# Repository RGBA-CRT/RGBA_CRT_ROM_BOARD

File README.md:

# RGBA_CRT ROM BOARD
+ 27C322 64Mbit ROM board for 8bit databus system
**※まだ不安定です**

# about
+ 27C322を40ピンのピンヘッダに引き出す基板です
+ レトロコンシューマゲーム機やレトロコンピュータでの使用を想定しています
+ 引き出したピンヘッダにはIDC 40ピンリボンケーブルを接続します
	+ IDEケーブル（40芯, 全ピンが結線されているもの）が使用可能です
+ その他
	+ データバスは8bitに変換されます
	+ 27C322を2つ使って64Mbitに対応
	+ ROMのセレクトスイッチ搭載
+ この基板に対応したROMライターはこちら
	+ https://github.com/RGBA-CRT/FT232H-EPROM-Prog

# PIN ROM Interface pinout

+ data bus: 8bit
+ address bus: A0-A23 24bit
+ control bus: CE / OE / WE
+ VPP signal supported

# ROM select switch
+ A20, A21, A22の制御スイッチがあります
	+ A20 ... 8Mbit単位切り替え
	+ A21 ... 16Mbit単位切り替え
	+ A22 ... 32Mbit単位切り替え（EPROM切り替え）
+ FREEにするとそのアドレスビットの制御を機器側に委ねます
+ FIXにするとそのアドレスビットの制御をHIGH/LOWスイッチに委ねます
+ 使用例
	+ 1つの64MbitのROMとして基板を使いたい
		+ A20, A21, A22をすべてFREEにする
	+ 4つの16MbitのROMとして基板を使いたい
		+ A20をFREEにする
		+ A21, A22はFIXにする
			+ 2つのHIGH/LOWスイッチで4分割したROMの選択を行う

# 使用例

# other
+ SNES/SFCのExHiROMとして使用する場合は、ROM焼き時と実機実行時でROM L, ROM Hを逆に取り付ける必要があります。
	+ ROMライターはファイルの順の通り次のように書き込みます
		+ ROM L: SNES BANK $C0-$FF
		+ ROM H: SNES BANK $40-$7F
	+ したがってSFCのカートリッジとして使うときにはROM LとROM Hを逆にする必要があります
+ おまけ
	+ この40 PIN ROM Interfaceに対応したユニバーサル基板

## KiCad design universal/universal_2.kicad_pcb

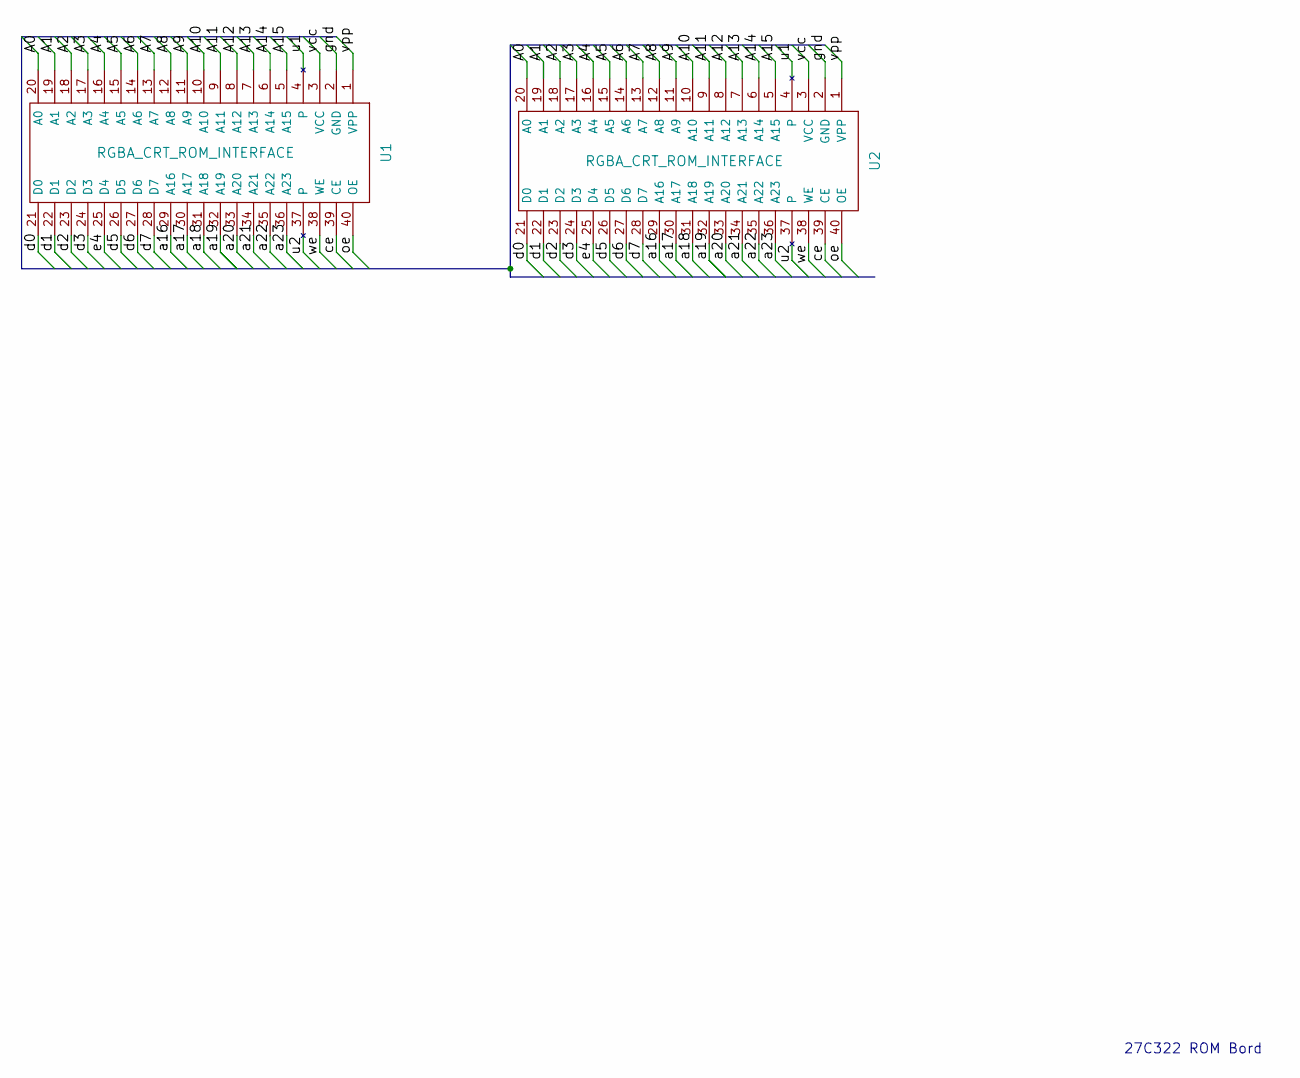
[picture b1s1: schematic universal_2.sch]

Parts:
U1: RGBA_CRT_ROM_INTERFACE
U2: RGBA_CRT_ROM_INTERFACE; RGBA_CRT_ROM_INTERFACE_DEBUG_HEDADER

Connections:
/A0: U1.20 (A0), U2.20 (A0)
/A1: U1.19 (A1), U2.19 (A1)
/A2: U1.18 (A2), U2.18 (A2)
/A3: U1.17 (A3), U2.17 (A3)
/A4: U1.16 (A4), U2.16 (A4)
/A5: U1.15 (A5), U2.15 (A5)
/A6: U1.14 (A6), U2.14 (A6)
/A7: U1.13 (A7), U2.13 (A7)
/A8: U1.12 (A8), U2.12 (A8)
/A9: U1.11 (A9), U2.11 (A9)
/A10: U1.10 (A10), U2.10 (A10)
/A11: U1.9 (A11), U2.9 (A11)
/A12: U1.8 (A12), U2.8 (A12)
/A13: U1.7 (A13), U2.7 (A13)
/A14: U1.6 (A14), U2.6 (A14)
/A15: U1.5 (A15), U2.5 (A15)
/a16: U1.29 (A16), U2.29 (A16)
/a17: U1.30 (A17), U2.30 (A17)
/a18: U1.31 (A18), U2.31 (A18)
/a19: U1.32 (A19), U2.32 (A19)
/a20: U1.33 (A20), U2.33 (A20)
/a21: U1.34 (A21), U2.34 (A21)
/a22: U1.35 (A22), U2.35 (A22)
/a23: U1.36 (A23), U2.36 (A23)
/ce: U1.39 (CE), U2.39 (CE)
/d0: U1.21 (D0), U2.21 (D0)
/d1: U1.22 (D1), U2.22 (D1)
/d2: U1.23 (D2), U2.23 (D2)
/d3: U1.24 (D3), U2.24 (D3)
/d5: U1.26 (D5), U2.26 (D5)
/d6: U1.27 (D6), U2.27 (D6)
/d7: U1.28 (D7), U2.28 (D7)
/e4: U1.25 (D4), U2.25 (D4)
/gnd: U1.2 (GND), U2.2 (GND)
/oe: U1.40 (OE), U2.40 (OE)
/u1: U1.4, U2.4
/u2: U1.37, U2.37
/vcc: U1.3 (VCC), U2.3 (VCC)
/vpp: U1.1 (VPP), U2.1 (VPP)
/we: U1.38 (WE), U2.38 (WE)

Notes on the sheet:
27C322 ROM Bord

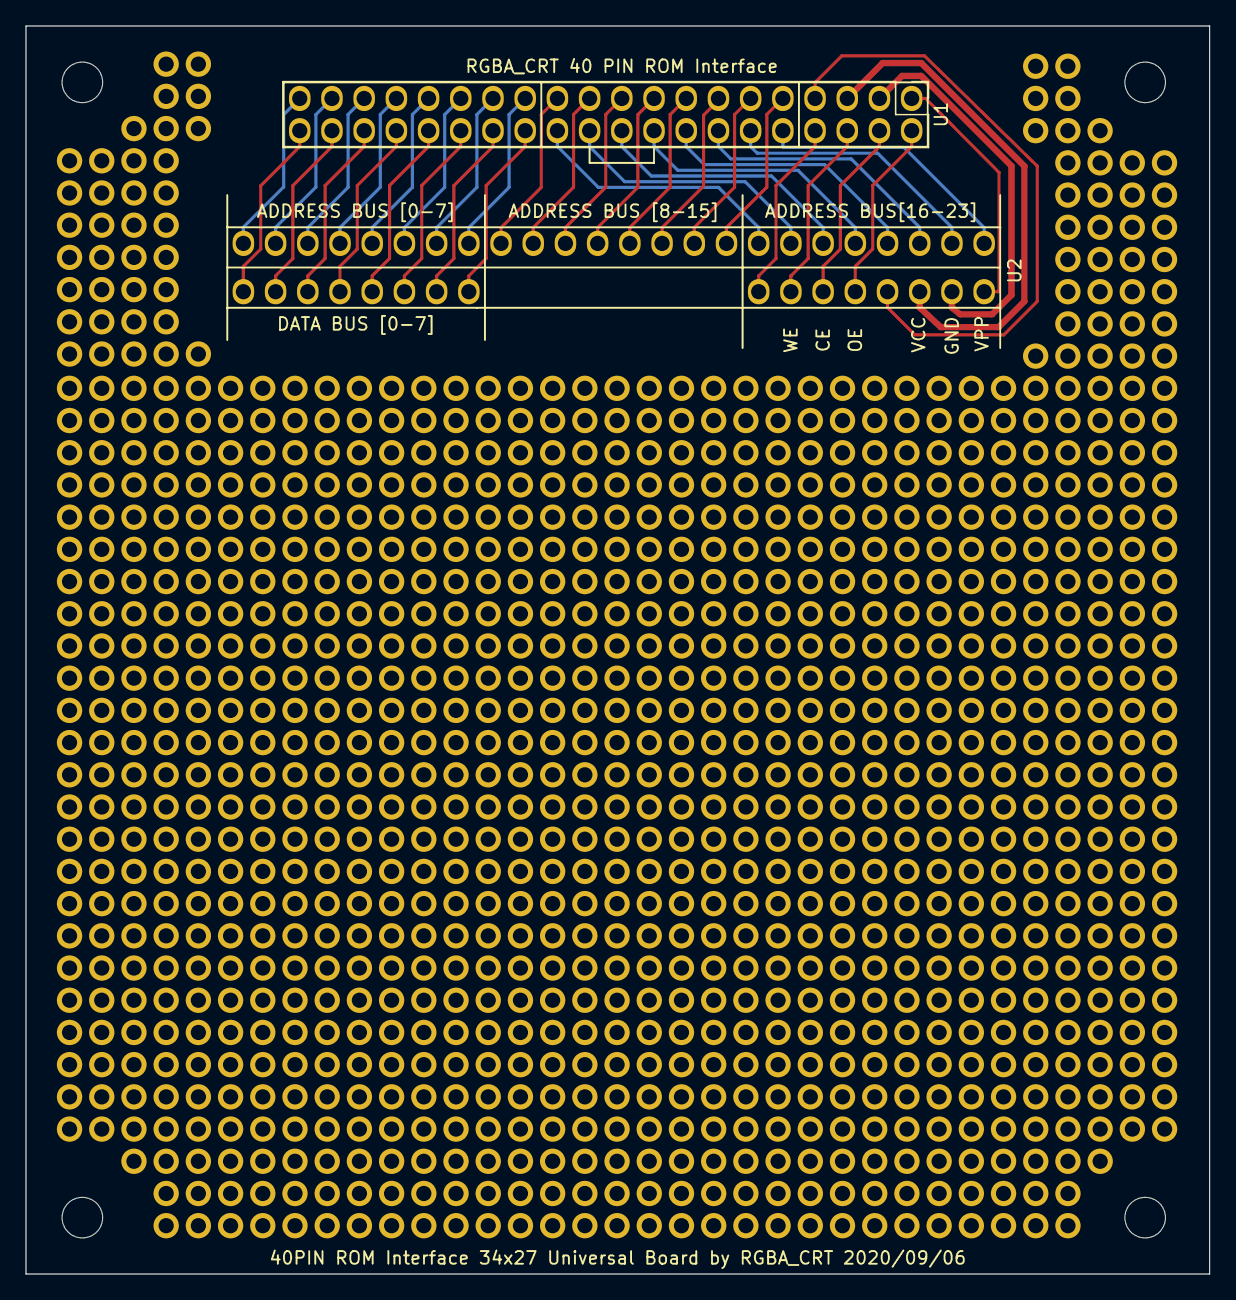
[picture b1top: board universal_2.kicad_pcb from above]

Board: 2 copper layers, 93.3 x 98.4 mm, 9 parts (0 on the bottom side), 40 nets.

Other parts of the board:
HOLE1, HOLE2, HOLE3, HOLE4: MountingHole_3.2mm_M3
LEFT: SolderWirePad_4xSquare_0-8mmDrill
RIGHT: SolderWirePad_4xSquare_0-8mmDrill
UBIVERSAL: SolderWirePad_4xSquare_0-8mmDrill

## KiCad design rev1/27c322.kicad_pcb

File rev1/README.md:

# RGBA_CRT_ROM_BOARD rev1
+ one ROM
+ 2 ROM select switch
+ low bytes are mapped to 0x000000-0x1FFFFF
+ high bytes are mapped to 0x200000-0x3FFFFF

# garber
[27c322Bord.zip](27c322Bord.zip)

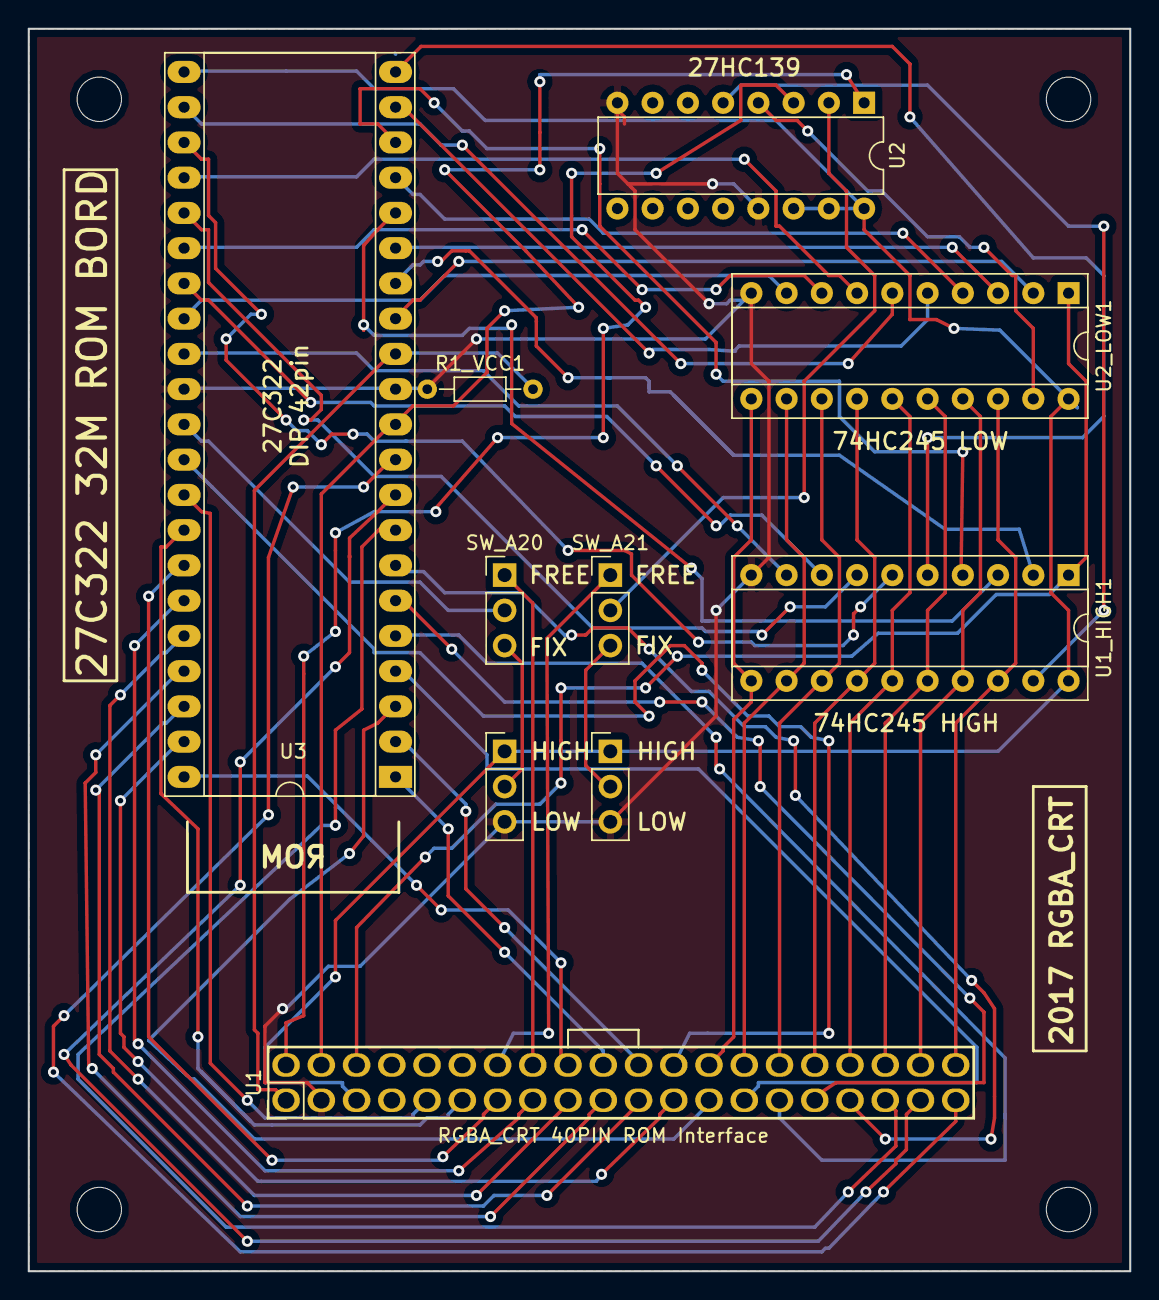
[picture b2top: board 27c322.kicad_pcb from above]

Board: 2 copper layers, 79.4 x 89.5 mm, 14 parts (0 on the bottom side), 58 nets.

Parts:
MOUNTU+: MountingHole_3.2mm_M3
MOUNT_BR: MountingHole_3.2mm_M3
MOUNT_LB: MountingHole_3.2mm_M3
MOUNT_UR: MountingHole_3.2mm_M3
R1_VCC1: R; R_Axial_DIN0204_L3.6mm_D1.6mm_P7.62mm_Horizontal
SWA21_HL1: Switch_SPDT_x2; Pin_Header_Straight_1x03_Pitch2.54mm
SW_A20, SW_A20_HL1, SW_A21: Switch_SPDT_x2; Pin_Header_Straight_1x03_Pitch2.54mm
U1: RGBA_CRT_ROM_INTERFACE
U1_HIGH1, U2_LOW1: 74HC245; DIP-20_W7.62mm_Socket
U2: 74LS139; DIP-16_W7.62mm
U3: 27C322; DIP-42_W15.24mm_Socket_LongPads

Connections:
+5V: SWA21_HL1.1, SW_A20_HL1.1, U1.3, U1_HIGH1.20, U2.14, U2.15, U2.16, U2_LOW1.20, U3.22
/A0: U1.20, U3.10
/A1: U1.19, U3.9
/A2: U1.18, U3.8
/A3: U1.17, U3.7
/A4: U1.16, U3.6
/A5: U1.15, U3.5
/A6: U1.14, U3.4
/A7: U1.13, U3.3
/A8: U1.12, U3.41
/A9: U1.11, U3.40
/A10: U1.10, U3.39
/A11: U1.9, U3.38
/A12: U1.8, U3.37
/A13: U1.7, U3.36
/A14: U1.6, U3.35
/A15: U1.5, U3.34
/A16: U1.29, U3.33
/A17: U1.30, U3.2
/A18: U1.31, U3.1
/A19: U1.32, U3.42
/A20: SW_A20.2, U3.32
/A21: SW_A21.2, U2.2
/D0: U1.21, U1_HIGH1.18, U2_LOW1.18
/D1: U1.22, U1_HIGH1.17, U2_LOW1.17
/D2: U1.23, U1_HIGH1.16, U2_LOW1.16
/D3: U1.24, U1_HIGH1.15, U2_LOW1.15
/D4: U1.25, U1_HIGH1.14, U2_LOW1.14
/D5: U1.26, U1_HIGH1.13, U2_LOW1.13
/D6: U1.27, U1_HIGH1.12, U2_LOW1.12
/D7: U1.28, U1_HIGH1.11, U2_LOW1.11
/FIX_A20: SW_A20.3, SW_A20_HL1.2
/FIX_A21: SWA21_HL1.2, SW_A21.3
/FREE_A20: SW_A20.1, U1.33
/FREE_A21: SW_A21.1, U1.34
/Q0: U2_LOW1.2, U3.14
/Q1: U2_LOW1.3, U3.16
/Q2: U2_LOW1.4, U3.18
/Q3: U2_LOW1.5, U3.20
/Q4: U2_LOW1.6, U3.23
/Q5: U2_LOW1.7, U3.25
/Q6: U2_LOW1.8, U3.27
/Q7: U2_LOW1.9, U3.29
/Q8: U1_HIGH1.2, U3.15
/Q9: U1_HIGH1.3, U3.17
/Q10: U1_HIGH1.4, U3.19
/Q11: U1_HIGH1.5, U3.21
/Q12: U1_HIGH1.6, U3.24
/Q13: U1_HIGH1.7, U3.26
/Q14: U1_HIGH1.8, U3.28
/Q15: U1_HIGH1.9, U3.30
GND: R1_VCC1.1, SWA21_HL1.3, SW_A20_HL1.3, U1.2, U1_HIGH1.10, U2.8, U2.13, U2_LOW1.10, U3.12, U3.31
unnamed: R1_VCC1.2, U1.1, U3.13
unnamed: U1.38, U1_HIGH1.1, U2_LOW1.1
unnamed: U1.39, U2.1, U3.11
unnamed: U1.40, U2.3
unnamed: U1_HIGH1.19, U2.5
unnamed: U2.4, U2_LOW1.19

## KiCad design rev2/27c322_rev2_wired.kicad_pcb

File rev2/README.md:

# RGBA_CRT_ROM_BOARD rev2
+ two ROM
+ 3 ROM select switch
+ low bytes are mapped to 0x0
+ high bytes are mapped to 0x1

# garber
[rev2.zip](rev2.zip)

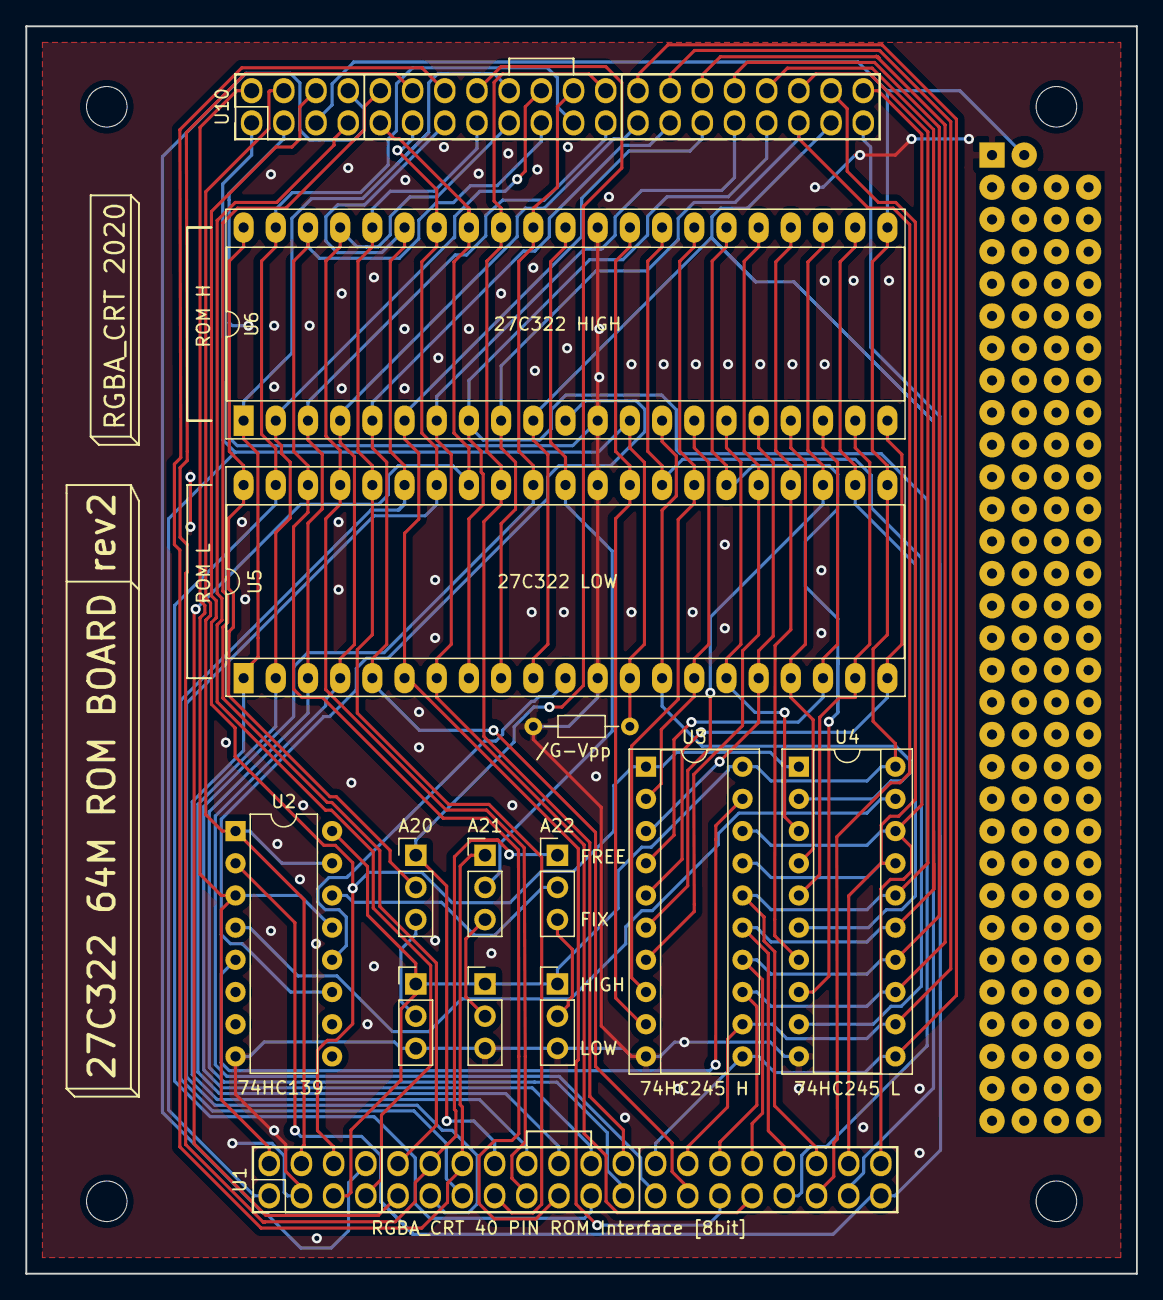
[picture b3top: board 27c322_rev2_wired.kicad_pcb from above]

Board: 2 copper layers, 87.6 x 98.4 mm, 21 parts (0 on the bottom side), 66 nets.

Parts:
/G-Vpp: R; R_Axial_DIN0204_L3.6mm_D1.6mm_P7.62mm_Horizontal
A20, A21, A22: Switch_SPDT_x2; Pin_Header_Straight_1x03_Pitch2.54mm
DR1, DR2, DR3, DR4: MountingHole_3.2mm_M3
GND: SolderWirePad_single_0-8mmDrill
SWA21_HL1: Switch_SPDT_x2; Pin_Header_Straight_1x03_Pitch2.54mm
SW_A20_HL1, SW_A22_HL1: Switch_SPDT_x2; Pin_Header_Straight_1x03_Pitch2.54mm
U1, U10: RGBA_CRT_ROM_INTERFACE
U2: 74LS139; DIP-16_W7.62mm
U3: 74HC245_H; DIP-20_W7.62mm_Socket
U4: 74HC245_L; DIP-20_W7.62mm_Socket
U5: 27C322_L; DIP-42_W15.24mm_Socket_LongPads
U6: 27C322_H; DIP-42_W15.24mm_Socket_LongPads
Universal Area: SolderWirePad_4xSquare_0-8mmDrill
VCC: SolderWirePad_single_0-8mmDrill

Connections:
+5V: SWA21_HL1.1, SW_A20_HL1.1, SW_A22_HL1.1, U1.3, U2.16, U3.20, U4.20, U5.22, U6.22, U10.3, VCC.1
/A0: U1.20, U2.2, U10.20
/A1: U1.19, U5.10, U6.10, U10.19
/A2: U1.18, U5.9, U6.9, U10.18
/A3: U1.17, U5.8, U6.8, U10.17
/A4: U1.16, U5.7, U6.7, U10.16
/A5: U1.15, U5.6, U6.6, U10.15
/A6: U1.14, U5.5, U6.5, U10.14
/A7: U1.13, U5.4, U6.4, U10.13
/A8: U1.12, U5.3, U6.3, U10.12
/A9: U1.11, U5.41, U6.41, U10.11
/A10: U1.10, U5.40, U6.40, U10.10
/A11: U1.9, U5.39, U6.39, U10.9
/A12: U1.8, U5.38, U6.38, U10.8
/A13: U1.7, U5.37, U6.37, U10.7
/A14: U1.6, U5.36, U6.36, U10.6
/A15: U1.5, U5.35, U6.35, U10.5
/A16: U1.29, U5.34, U6.34, U10.29
/A17: U1.30, U5.33, U6.33, U10.30
/A18: U1.31, U5.2, U6.2, U10.31
/A19: U1.32, U5.1, U6.1, U10.32
/A20: A20.2, U5.42, U6.42
/A21: A21.2, U5.32, U6.32
/A22: A22.2, U2.14
/D0: U1.21, U3.18, U4.18, U10.21
/D1: U1.22, U3.17, U4.17, U10.22
/D2: U1.23, U3.16, U4.16, U10.23
/D3: U1.24, U3.15, U4.15, U10.24
/D4: U1.25, U3.14, U4.14, U10.25
/D5: U1.26, U3.13, U4.13, U10.26
/D6: U1.27, U3.12, U4.12, U10.27
/D7: U1.28, U3.11, U4.11, U10.28
/IF_A20: A20.1, U1.33, U10.33
/IF_A21: A21.1, U1.34, U10.34
/IF_A22: A22.1, U1.35, U10.35
/IF_A23: U1.36, U10.36
/OE: U1.40, U2.3, U2.13, U10.40
/Q0: U4.2, U5.14, U6.14
/Q1: U4.3, U5.16, U6.16
/Q2: U4.4, U5.18, U6.18
/Q3: U4.5, U5.20, U6.20
/Q4: U4.6, U5.23, U6.23
/Q5: U4.7, U5.25, U6.25
/Q6: U4.8, U5.27, U6.27
/Q7: U4.9, U5.29, U6.29
/Q8: U3.2, U5.15, U6.15
/Q9: U3.3, U5.17, U6.17
/Q10: U3.4, U5.19, U6.19
/Q11: U3.5, U5.21, U6.21
/Q12: U3.6, U5.24, U6.24
/Q13: U3.7, U5.26, U6.26
/Q14: U3.8, U5.28, U6.28
/Q15: U3.9, U5.30, U6.30
GND: /G-Vpp.2, GND.1, SWA21_HL1.3, SW_A20_HL1.3, SW_A22_HL1.3, U1.2, U2.8, U3.10, U4.10, U5.12, U5.31, U6.12, U6.31, U10.2
unnamed: /G-Vpp.1, U1.1, U5.13, U6.13, U10.1
unnamed: A21.3, SWA21_HL1.2
unnamed: A20.3, SW_A20_HL1.2
unnamed: A22.3, SW_A22_HL1.2
unnamed: U1.4, U10.4
unnamed: U1.37, U10.37
unnamed: U1.38, U3.1, U4.1, U10.38
unnamed: U1.39, U2.1, U2.15, U10.39
unnamed: U2.4, U4.19
unnamed: U2.5, U3.19
unnamed: U2.11, U6.11
unnamed: U2.12, U5.11

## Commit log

2021-02-14 add README
2021-02-14 add switch description
